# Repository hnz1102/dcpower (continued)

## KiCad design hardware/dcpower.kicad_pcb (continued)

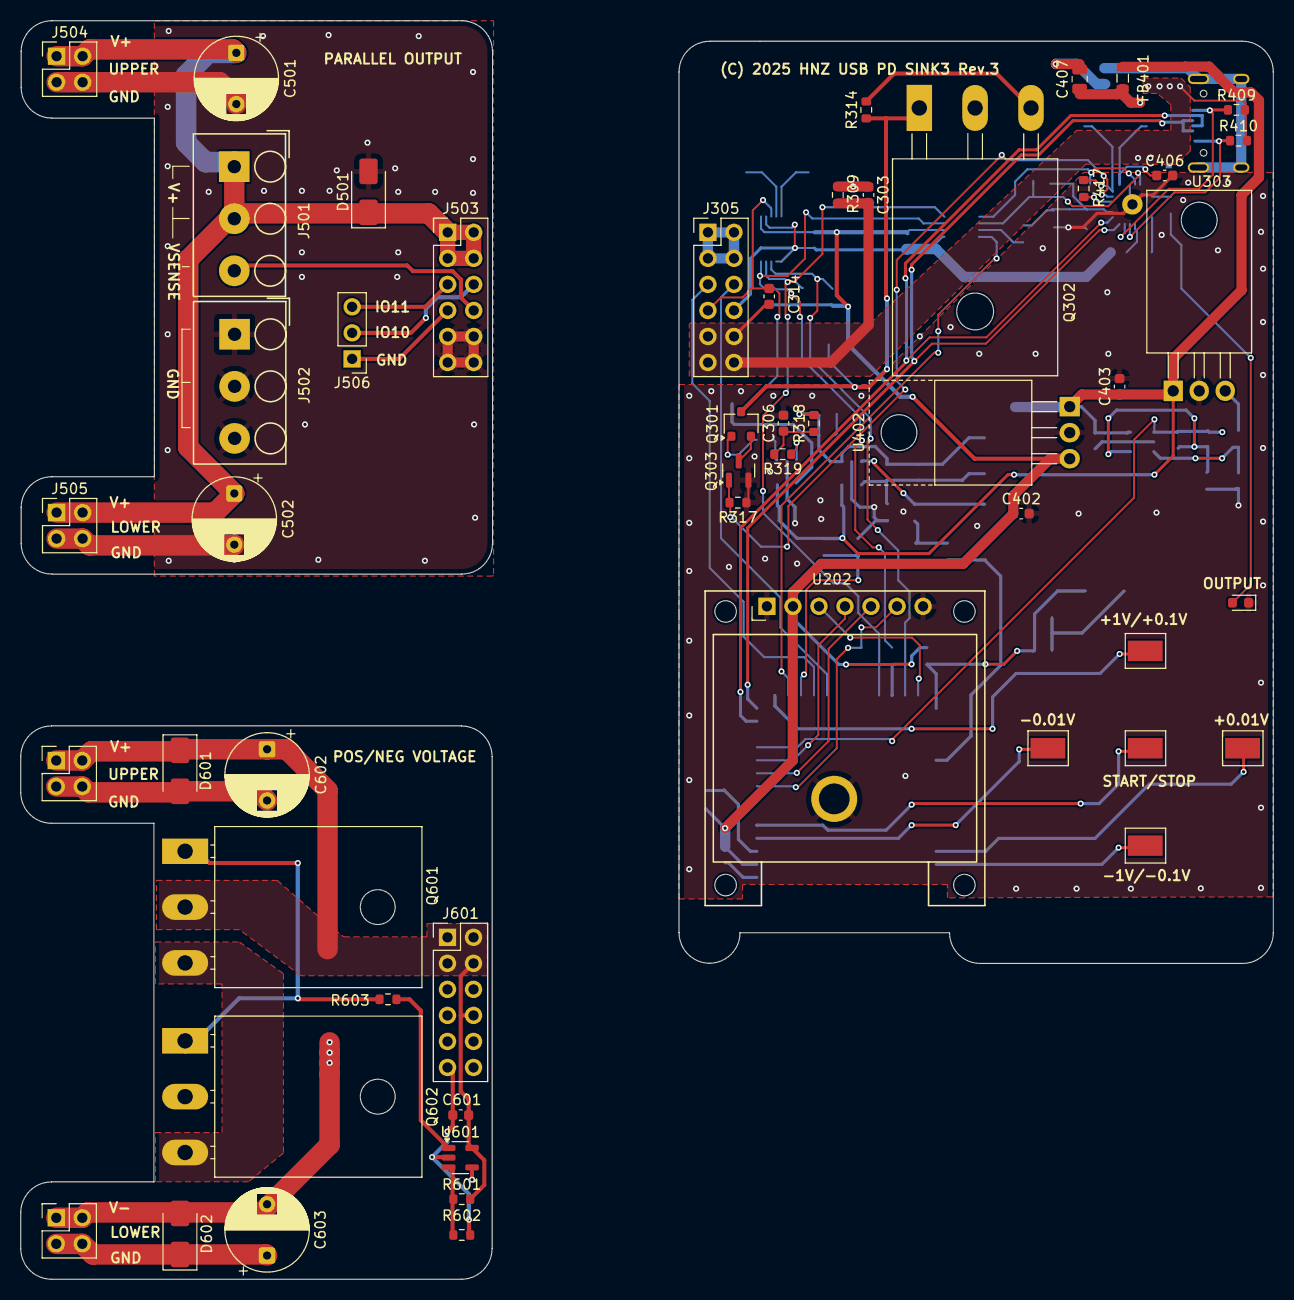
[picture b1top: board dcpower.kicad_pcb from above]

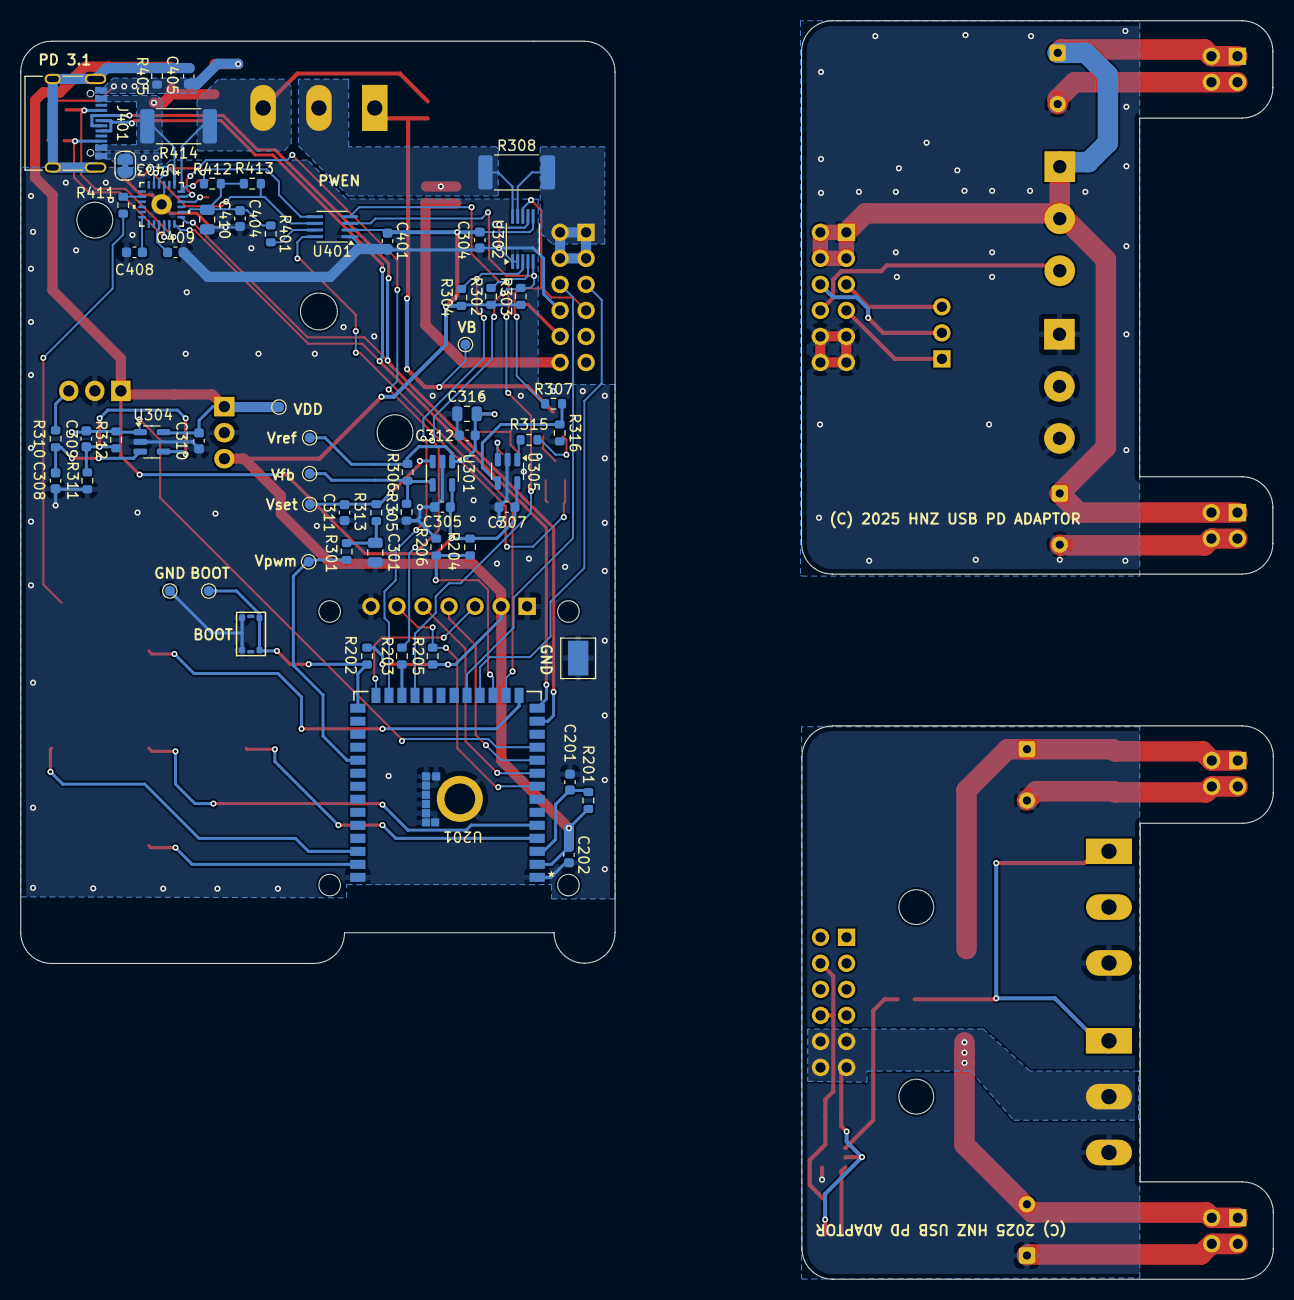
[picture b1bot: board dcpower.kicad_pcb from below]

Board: 2 copper layers, 58.0 x 90.0 mm, 115 parts (63 on the bottom side), 68 nets.

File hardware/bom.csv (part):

"Reference","Value","Datasheet","Footprint","Qty","DNP","digikey","distributor","storeURL"
"C201,C202,C304,C308,C401,C402,C404,C405,C409","0.1uF","~","Capacitor_SMD:C_0603_1608Metric","9","","311-1343-1-ND","https://www.digikey.com/en/products/detail/yageo/CC0603ZRY5V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",""
"C301","10uF","~","Capacitor_SMD:C_0805_2012Metric","1","","490-6473-1-ND","https://www.digikey.com/en/products/detail/murata-electronic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",""
"C303,C305,C306,C307,C310,C314,C406,C408,C601","0.1uF/50V","~","Capacitor_SMD:C_0603_1608Metric","9","","311-1343-1-ND","https://www.digikey.com/en/products/detail/yageo/CC0603ZRY5V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",""
"C309","1000pF","~","Capacitor_SMD:C_0603_1608Metric","1","","311-1080-1-ND","https://www.digikey.com/en/products/detail/yageo/CC0603KRX7R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",""
"C311","47pF","~","Capacitor_SMD:C_0603_1608Metric","1","","311-3980-1-ND","https://www.digikey.com/en/products/detail/yageo/CC0603JRNPO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",""
"C312","0.01uF/50V","~","Capacitor_SMD:C_0603_1608Metric","1","","311-1085-1-ND","https://www.digikey.com/en/products/detail/yageo/CC0603ZRY5V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",""
"C316,C407","10uF/50V","~","Capacitor_SMD:C_0805_2012Metric","2","","490-18663-1-ND","https://www.digikey.com/en/products/detail/murata-electronic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",""
"C403","0.47uF/50V","~","Capacitor_SMD:C_0603_1608Metric","1","","587-3170-1-ND","https://www.digikey.com/en/products/detail/taiyo-yuden/UMK10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",""
"C410","1uF","~","Capacitor_SMD:C_0805_2012Metric","1","","311-1365-1-ND","https://www.digikey.jp/en/products/detail/yageo/CC0805KKX7R7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",""
"C501,C502,C602,C603","470uF","~","Capacitor_THT:CP_Radial_D8.0mm_P5.00mm","4","","1189-1890-ND","",""
"D402","LED BLUE","~","LED_SMD:LED_0603_1608Metric","1","","3147-B1931NB--20C007614U1930CT-ND","",""
"D501,D601,D602","SK36A-LTP","","Diode_SMD:D_SMA","3","","SK36A-LTPMSCT-ND","https://www.digikey.com/en/products/detail/mcc-micro-commerc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",""
"FB401","MH2029-601Y","~","Inductor_SMD:L_0805_2012Metric","1","","MH2029-601YCT-ND","https://www.digikey.com/en/products/detail/bourns-inc/MH2029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",""
"J305","PINOUT","~","Connector_PinHeader_2.54mm:PinHeader_2x06_P2.54mm_Vertical","1","","PPPC062LJBN-RC","https://www.digikey.com/en/products/detail/sullins-connector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",""
"J401","USB4105-GF-A","https://www.usb.org/sites/default/files/documents/usb_type-c.zip","Library:USB_C_5077CR-16-SMC2-BK-TR","1","","2073-USB4105-GF-ACT-ND","https://www.digikey.com/en/products/detail/gct/USB4105-GF-A/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",""
"J501,J502","Screw_Terminal_3P","~","Library:TB112-2-2-3-E-1 Terminal Block","2","","A113321-ND","https://akizukidenshi.com/catalog/g/g101310/",""
"J503,J601","ADPIN","~","Connector_PinHeader_2.54mm:PinHeader_2x06_P2.54mm_Vertical","2","","2057-PH2RA-12-UA-ND","",""
"J504,J602","UPPER OUT","~","Connector_PinHeader_2.54mm:PinHeader_2x02_P2.54mm_Vertical","2","","2057-PH2-04-UA-ND","",""
"J505,J603","LOWER OUT","~","Connector_PinHeader_2.54mm:PinHeader_2x02_P2.54mm_Vertical","2","","2057-PH2-04-UA-ND","",""
"J506","GPIO","~","Connector_PinHeader_2.54mm:PinHeader_1x03_P2.54mm_Vertical","1","","2057-RS1-03-G-ND","",""
"JP301","Jumper","~","Jumper:SolderJumper-2_P1.3mm_Bridged_RoundedPad1.0x1.5mm","1","","-","",""
"Q301","2SC3325","","Package_TO_SOT_SMD:SC-59","1","","2SC3325-YLFCT-ND","",""
"Q302","IRFP9140NPBF","","Package_TO_SOT_THT:TO-247-3_Horizontal_TabUp","1","","IRFP9140NPBF-ND","https://www.digikey.com/en/products/detail/infineon-technolo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",""
"Q303","2N7002K","https://www.diodes.com/assets/Datasheets/ds30896.pdf","Package_TO_SOT_SMD:SOT-23","1","","2N7002KCT-ND","",""
"Q601","2SC5200","","Package_TO_SOT_THT:TO-3P-3_Horizontal_TabDown","1","","5272-2SC5200-ND","https://www.digikey.com/en/products/detail/evvo/2SC5200/22674673",""
"Q602","2SA1943","","Package_TO_SOT_THT:TO-3P-3_Horizontal_TabDown","1","","5272-2SA1943-ND","https://www.digikey.com/en/products/detail/evvo/2SA1943/22674744",""
"R201,R202,R205,R302,R303,R304,R405","10K","~","Resistor_SMD:R_0603_1608Metric","7","","13-RC0603JR-1010KLCT-ND","https://www.digikey.com/en/products/detail/yageo/RC0603JR-10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",""
"R203","150","~","Resistor_SMD:R_0603_1608Metric","1","","311-150GRCT-ND","https://www.digikey.jp/en/products/detail/yageo/RC0603JR-071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",""
"R204","47K 1%","~","Resistor_SMD:R_0603_1608Metric","1","","311-47.0KHRCT-ND","https://www.digikey.com/en/products/detail/yageo/RC0603FR-07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",""
"R206","4.7K 1%","~","Resistor_SMD:R_0603_1608Metric","1","","311-4.70KHRCT-ND","https://www.digikey.com/en/products/detail/yageo/RC0603FR-07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",""
"R301,R306,R309,R310,R316,R317,R318,R319,R601,R602","10K 1%","~","Resistor_SMD:R_0603_1608Metric","10","","311-10.0KHRCT-ND","https://www.digikey.com/en/products/detail/yageo/RC0603FR-07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,https://www.digikey.jp/en/products/detail/yageo/RC0603FR-071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",""
"R305,R307,R311,R312","1K 1%","~","Resistor_SMD:R_0603_1608Metric","4","","YAG2323CT-ND","https://www.digikey.com/en/products/detail/yageo/RC0603FR-07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,https://www.digikey.jp/en/products/detail/yageo/RC0603FR-071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",""
"R308,R414","5m","~","Resistor_SMD:R_2512_6332Metric_Pad1.40x3.35mm_HandSolder","2","","4506-PEWF2512D5L00Q9CT-ND ","https://www.digikey.com/en/products/detail/resi/PEWF2512D5L0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,https://www.digikey.jp/en/products/detail/resi/PEWF2512D5L00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",""
"R313","3.09K 1%","~","Resistor_SMD:R_0603_1608Metric","1","","311-3.09KHRCT-ND","https://www.digikey.com/en/products/detail/yageo/RC0603FR-07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",""
"R314,R411","1K","~","Resistor_SMD:R_0603_1608Metric","2","","13-RC0603JR-1010KLCT-ND","https://www.digikey.com/en/products/detail/yageo/RC0603JR-10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,https://www.digikey.jp/en/products/detail/yageo/RC0603FR-071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",""
"R315","100K 1%","~","Resistor_SMD:R_0603_1608Metric","1","","311-100KHRCT-ND","https://www.digikey.jp/en/products/detail/yageo/RC0603FR-071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",""
"R401","200K","~","Resistor_SMD:R_0603_1608Metric","1","","311-200KHRCT-ND","https://www.digikey.com/en/products/detail/yageo/RC0603FR-07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",""
"R409,R410","5K1","~","Resistor_SMD:R_0603_1608Metric","2","","311-5.10KHRCT-ND","https://www.digikey.com/en/products/detail/yageo/RC0603FR-07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",""
"R412,R413","4.7K","~","Resistor_SMD:R_0603_1608Metric","2","","311-4.70KHRCT-ND","https://www.digikey.jp/en/products/detail/yageo/RC0603FR-074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",""
"R417","100","~","Resistor_SMD:R_0603_1608Metric","1","","311-100GRCT-ND","https://www.digikey.jp/en/products/detail/yageo/RC0603JR-071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",""
"R603","220","~","Resistor_SMD:R_0603_1608Metric","1","","311-220GRCT-ND","https://www.digikey.com/en/products/detail/yageo/RC0603JR-07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",""
"SW201","3.5x2.6 Tact SW","","Library:WS-TASV SMT Tact Switch","1","","732-435151014824CT-ND","https://www.digikey.com/en/products/detail/w%C3%BCrth-elektr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",""
"TP-PAD201","TOUCH1","~","Library:TestPoint_Pad_3.2x1.6mm","1","","-","",""
"TP-PAD202","TOUCH2","~","Library:TestPoint_Pad_3.2x1.6mm","1","","-","",""
"TP-PAD203","TOUCH3","~","Library:TestPoint_Pad_3.2x1.6mm","1","","-","",""
"TP-PAD204","TOUCH4","~","Library:TestPoint_Pad_3.2x1.6mm","1","","-","",""
"TP-PAD205","TOUCH5","~","Library:TestPoint_Pad_3.2x1.6mm","1","","-","",""
"TP-PAD301","TPGND","~","Library:TestPoint_Pad_3.2x1.6mm","1","","2019-RCWCTECT-ND","https://www.digikey.com/en/products/detail/koa-speer-electro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",""
"TP202","BOOT","~","TestPoint:TestPoint_Pad_D1.0mm","1","","-","",""
"TP301","PWM","~","TestPoint:TestPoint_Pad_D1.0mm","1","","-","",""
"TP302","SET-Vr","~","TestPoint:TestPoint_Pad_D1.0mm","1","","-","",""
"TP303","Vfb","~","TestPoint:TestPoint_Pad_D1.0mm","1","","-","",""
"TP304","OP-VCC","~","TestPoint:TestPoint_Pad_D1.0mm","1","","-","",""
"TP306","Vb","~","TestPoint:TestPoint_Pad_D1.0mm","1","","-","",""
"TP309","GND","~","TestPoint:TestPoint_Pad_D1.0mm","1","","-","",""
"TP310","Vref","~","TestPoint:TestPoint_Pad_D1.0mm","1","","-","",""
"U201","ESP32-S3-WROOM-1-N16R8","ESP32-S3-WROOM-1-N16R2","Library:ESP32-S3-WROOM-1_EXP","1","","1965-ESP32-S3-WROOM-1-N16R8CT-ND","https://www.digikey.com/en/products/detail/espressif-systems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",""
"U202","SSD1331_DISPLAY","","Library:OLED SSD1331 SPI DISPLAY","1","","3190-DLC0095ANOB-1-ND","https://akizukidenshi.com/catalog/g/gP-14435/",""
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
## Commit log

2025-09-14 Update package
2025-09-15 Change partition type
2025-09-15 Under Developtment
2025-09-15 Add images
2025-09-27 Add safty functions
2025-09-27 Update influxdb dashboard template
2025-09-28 Added NVS (Non-Volatile Storage) functionality to save the last set voltage when load starts and restore it as the initial voltage setting on next boot.
2025-09-28 Add hardware data
2025-10-13 Fixed BOM list and README
2025-10-19 for update ap33772s-driver
2025-10-19 update ap33772s-driver
